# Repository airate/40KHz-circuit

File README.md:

# 40KHz-circuit
Drive a circuit at 40KHz

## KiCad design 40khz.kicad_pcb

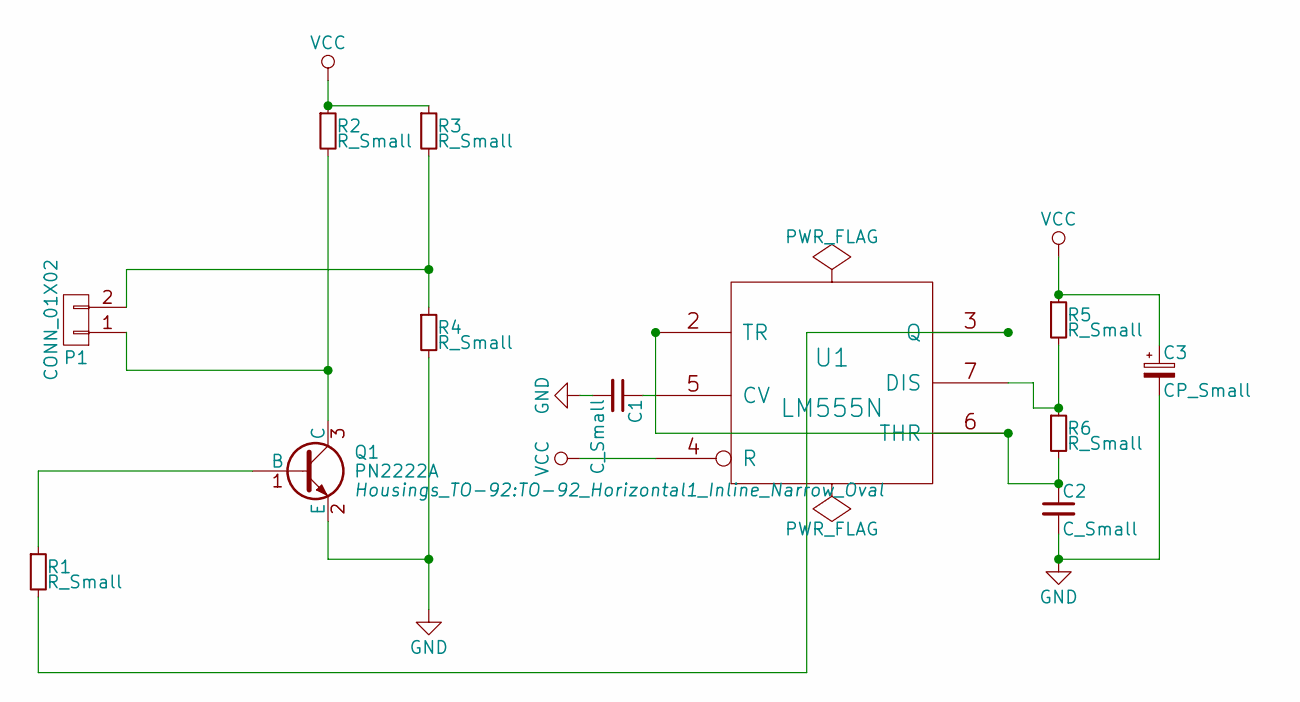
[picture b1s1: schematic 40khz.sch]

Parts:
C1, C2: C_Small; C_0402
C3: CP_Small; SMD-1210_Pol
P1: CONN_01X02; Pin_Header_Angled_1x02
Q1: PN2222A; TO-92_Horizontal1_Inline_Narrow_Oval
R1, R2, R3, R4, R5, R6: R_Small; R_0402
U1: LM555N; DIP-8_W7.62mm_LongPads

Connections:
GND: C1.2, C2.2, C3.2, Q1.2 (E), R4.2, U1.1 (GND)
unnamed: C1.1, U1.5 (CV)
unnamed: C2.1, R6.2, U1.2 (TR), U1.6 (THR)
unnamed: P1.1, Q1.3 (C), R2.2
unnamed: P1.2, R3.2, R4.1
unnamed: Q1.1 (B), R1.1
unnamed: R1.2, U1.3 (Q)
unnamed: R5.2, R6.1, U1.7 (DIS)
VCC: C3.1, R2.1, R3.1, R5.1, U1.4 (R), U1.8 (VCC)

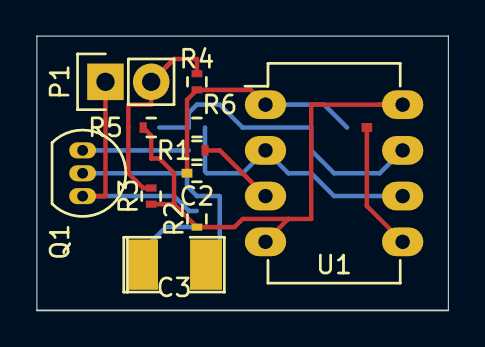
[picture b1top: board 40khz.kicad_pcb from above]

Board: 2 copper layers, 22.9 x 15.2 mm, 12 parts (1 on the bottom side), 9 nets.
